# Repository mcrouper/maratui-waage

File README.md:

<p align="center">
    
    <br><br>
    
</p>

# MaraTUI

An embedded Rust TUI application for the **Lelit Mara X** espresso machine. Runs on an **ESP32** microcontroller driving an **ILI9341 320×240 display** over SPI, reads machine telemetry over UART, and publishes events to MQTT. Includes a host simulator mode for UI development without any hardware.

## Screenshots

| Loading | Dashboard | Debug |
|---------|-----------|-------|
|  |  |  |

## Screens

Navigation cycles between two main screens with a button press. The Debug screen is a hidden overlay.

### Dashboard

The primary screen. Shows all real-time machine data:

- **Mode banner** — COFFEE / STEAM / OFFLINE, color-coded
- **Boiler gauge** — current vs. target temperature with warm→ready color zones and a target marker
- **HX column** — heat-exchanger temperature with a vertical mini-gauge; ideal zone (90–95°C) is always visible
- **HEAT / PUMP indicators** — live status dots
- **Extraction timer** — large anti-aliased seconds counter; after the shot an assessment (GOOD, PERFECT, …) appears in its bottom border
- **Weight** — live shot weight in grams from the dual-HX711 scale, auto-tared the moment the pump starts
- **Shot gauge ("%")** — tracks extracted weight against a 40g target, not elapsed time
- **Shot quality label** — post-extraction assessment (UNDEREXTRACTED / GOOD / PERFECT / LONG SHOT / BLONDING) shown after the pump stops
- **Cup counter** — total shots brewed, received via MQTT
- **Tank water** — remaining water in the 2.3 L tank, tracked per pump run (weighed on the scale, or estimated from pump time) and saved across reboots; at 150 ml or less a popup asks to confirm the refill with a short press

### Graphs

Temperature history chart over a **5-minute rolling window** sampled at 1 Hz:

- Boiler current temperature (yellow)
- Boiler target temperature (red)
- HX temperature (blue)

### Debug (hidden overlay)

Accessible via long press. Shows Wi-Fi and MQTT connection statuses, device info (SSID, RSSI, IP, uptime, free heap), live raw UART frame with activity indicator, and the last 10 telemetry events.

## Getting Started

### Simulator

The simulator runs on your host machine using SDL2 for display emulation — no ESP32 needed.

**Prerequisites:** install SDL2 development libraries for your OS ([installation guide](https://docs.rs/crate/sdl2/latest/source/README.md)).

```bash
make sim          # auto-detects OS
```

Or use platform-specific cargo aliases:

| OS      | Command        |
|---------|----------------|
| Linux   | `cargo sim`    |
| macOS   | `cargo simmac` |
| Windows | `cargo simwin` |

**Keyboard controls:**

| Key          | Action                        |
|--------------|-------------------------------|
| Right / Left | Toggle Dashboard ↔ Graphs     |
| D            | Toggle Debug overlay          |
| Up           | Inject pump-on debug frame    |
| Down         | Inject normal debug frame     |
| Space        | Inject no-water debug frame   |
| M            | Publish manual MQTT event     |

### Device (ESP32)

**Prerequisites:** Rust with the `esp` toolchain channel (pinned in `rust-toolchain.toml`).

```bash
cargo run --release
```

Uses `espflash flash --monitor` as the runner. On startup the firmware:

1. Connects to Wi-Fi using embedded credentials
2. Starts the MQTT client and subscribes to `<prefix>/cup_counter`
3. Streams telemetry to `<prefix>/telemetry` (~1 Hz)
4. Publishes events (shot start/end, water refill, mode change) to `<prefix>/events`
5. Publishes device status (IP, RSSI, uptime, heap) to `<prefix>/status`

## Configuration

Copy `.env.example` to `.env` (git-ignored) and fill in your values:

```bash
cp .env.example .env
```

| Variable | Description |
|---|---|
| `MARATUI_WIFI_SSID` / `_PASSWORD` | Wi-Fi credentials (device build only) |
| `MARATUI_MQTT_ENABLED` | Set `true` to enable MQTT publishing |
| `MARATUI_MQTT_URL` | Broker URL, e.g. `mqtt://192.168.1.x:1883` |
| `MARATUI_MQTT_CLIENT_ID` | Unique client identifier |
| `MARATUI_MQTT_TOPIC_PREFIX` | Topic namespace prefix (default: `mara`) |

> [!NOTE]
> On the ESP32 build (`device` feature), `.env` is parsed by `build.rs` and values are embedded at compile time. On the simulator (`simulator` feature), env values are read at runtime and Wi-Fi is skipped — host networking is used directly for MQTT.

> [!WARNING]
> Wi-Fi and MQTT credentials are stored as plaintext `&'static str` in the flash image. Rotate credentials if the device is shared or its firmware is distributed. See the [Security Considerations](#security-considerations) section below.

## Home Assistant Integration

Build with `--features home-assistant` to enable MQTT Discovery publishing directly from the firmware — no Node-RED or other bridge required. On every MQTT connect, retained discovery configs are published and entities appear in Home Assistant automatically.

```bash
cargo run --release --features home-assistant   # flash
make sim-ha                                      # simulator
```

See [docs/home-assistant.md](docs/home-assistant.md) for the full entity list, MQTT topic reference, and cup counter setup.

## Web Dashboard

A standalone live dashboard page (temperatures with history, live scale weight, shot timer and weight curve, recent shots, events, device status) served by Node-RED at `http://<node-red-host>:1880/mara`, deployed with `python3 dashboard/deploy.py`. See [dashboard/README.md](dashboard/README.md).

## Color Editor

`python3 tools/color_editor.py` (Python 3 with Tkinter, no other dependencies) opens a drag-and-drop editor for the Dashboard and start screen colors: drag a swatch onto an element in the preview, then "Speichern" writes the palette constants back into `src/screens/dashboard.rs` and `src/screens/connecting.rs` — rebuild and flash to apply. Its "Startvideo" page plays the boot animation rendered by the firmware's own scene code (`examples/boot_frames.rs`, needs the host Rust toolchain), so animation changes can be previewed without flashing.

## Hardware

Target board: **ESP32 Type-C** with an external **ILI9341** 240×320 TFT display connected over SPI. There is a single physical button.

| Press             | Action                          |
|-------------------|---------------------------------|
| Short             | Zero the scale (confirms the tank refill while the low-water warning shows) |
| Double (fast 2x)  | Toggle Dashboard ↔ Graphs       |
| Double (on loading)| Toggle display backlight       |
| Long              | Enter / exit Debug overlay      |
| Hold (3s)         | Start the scale calibration wizard |

See [`hardware/`](hardware/) for the KiCad project, PCB renders, Gerber files, and full ESP32 pinout and display wiring.

### Scale (dual HX711 load cells)

Two independent HX711 amplifiers — one per drip-tray side — feed the live Weight display and
the weight-based shot gauge. Hold the button for 3s to run the calibration wizard (tare, then a
known reference weight, for each cell in turn); results persist to NVS. The scale also auto-tares
at boot and at the start of every shot; a short press zeroes it manually at any time. See
[`docs/hardware.md`](docs/hardware.md) for wiring and the full calibration walkthrough.

|  |  |  |
|:---:|:---:|:---:|

## Security Considerations

- **Credentials in flash** — Wi-Fi and MQTT credentials are embedded at compile time and extractable from the flash image with standard tools (`strings`, `binwalk`). Rotate if the device is shared.
- **Default broker is public** — `mqtt://broker.emqx.io:1883` is a free public broker with no access control. Set a private broker with authentication before deploying.
- **No TLS** — traffic is plaintext TCP. Switch to `mqtts://` and configure a CA certificate for production use.
- **Open Wi-Fi fallback** — if `MARATUI_WIFI_PASSWORD` is empty, `AuthMethod::None` is used (no encryption). A startup `warn!` names the SSID to make this explicit.

## Roadmap

- Offline mode using NVS storage

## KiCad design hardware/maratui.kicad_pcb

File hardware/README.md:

# MaraTUI PCB

Custom ESP32 controller board for the [Lelit Mara X](https://lelitcoffee.com/product/mara-x/) espresso machine.

## PCB Render

## Components

| Ref | Part | Link |
|-----|------|------|
| U1 | ILI9341 2.8" SPI TFT with touch | [Amazon TR](https://www.amazon.com.tr/2-8in%C3%A7-SPI-Dokunmatik-Ekran-Mod%C3%BCl%C3%BC/dp/B0GWFFJBZN) |
| U2 | ESP32-WROOM-32 | [Amazon TR](https://www.amazon.com.tr/ESP32-Wroom-32-Wifi-Bluetooth-Geli%C5%9Ftirme-Kart%C4%B1/dp/B0BT7SW1LF) |
| SW1 | Tactile switch | |
| J1 | Barrel jack (power) | |
| J2 | 3-pin connector (GND + UART) | |
| U3, U4 | HX711 load-cell amplifier (one per scale cell) | |

## Wiring

### SPI Display (ILI9341)

| Display Pin | ESP32 GPIO | Notes |
|-------------|------------|-------|
| SCK / CLK   | GPIO18     | VSPI CLK |
| SDA / MOSI  | GPIO21     | VSPI MOSI |
| DC / RS     | GPIO23     | Data/Command select |
| CS          | GPIO19     | Chip Select |
| RST / RESET | GPIO22     | Hardware reset |
| LED / BLK   | GPIO14     | Backlight (HIGH = on) |
| VCC         | 3.3V       | |
| GND         | GND        | |

### UART (Lelit Mara X telemetry)

| Function | ESP32 GPIO | Notes |
|----------|------------|-------|
| TX       | GPIO17     | UART1 TX |
| RX       | GPIO16     | UART1 RX |

### Scale (dual HX711 load cells)

| HX711 Pin    | ESP32 GPIO | Notes |
|--------------|------------|-------|
| DOUT (left)  | GPIO25     | Data, left load cell (input on ESP32) |
| SCK (left)   | GPIO26     | Clock, left load cell (output from ESP32) |
| DOUT (right) | GPIO32     | Data, right load cell (input on ESP32) |
| SCK (right)  | GPIO27     | Clock, right load cell (output from ESP32) |

Each HX711 has its **own** DOUT and SCK line (not shared) so the two cells can be clocked and
read independently — one under each side of the drip tray. See
[`docs/hardware.md`](../docs/hardware.md) for E+/E-/A+/A- load-cell wiring and the calibration
procedure.

### Button

| Button   | ESP32 GPIO | Notes |
|----------|------------|-------|
| SW1      | GPIO12     | Internal pull-up enabled |

Button connects GPIO to **GND** via a tactile switch (active LOW, falling-edge detection).

- Short press (< 500 ms): cycle screens (Dashboard ↔ Graphs)
- Double press (two short presses within 400 ms): zero the scale
- Long press (≥ 500 ms): toggle Debug screen
- Hold (3 s): start the scale calibration wizard

## Custom Libraries

Non-standard components are bundled in `lib/` so the project opens without missing library errors on any machine.

| File | Description |
|------|-------------|
| `lib/symbols/esp32_30pin.kicad_sym` | ESP32-WROOM-32 symbol |
| `lib/symbols/tft_320x240.kicad_sym` | ILI9341 320×240 symbol |
| `lib/footprints/maratui.pretty/ESP32_30pin.kicad_mod` | ESP32 footprint |
| `lib/footprints/maratui.pretty/TFT-320x240.kicad_mod` | TFT display footprint |

## Manufacturing

Gerber + drill files for fabrication: `gerbers/Mara_waage.zip` (single board, scale cells included; the same files also lie unpacked in `gerbers/`)

Tested with JLCPCB default 2-layer settings.

## 3D-Printed Parts (`3d-print/`)

Printable parts (STEP source + STL for slicing; versions in the file name):

| File | Description |
|------|-------------|
| `geh_koerper_V3.stp` / `geh_koerper_v3.stl` | Enclosure body (v3) — rear shell for ESP32 and PCB, cable/USB openings |
| `geh_deckel_V3.stp` / `geh_deckel_v3.stl` | Enclosure lid (v3) — front bezel with the display window |
| `doppelfuss_V2.stp` / `doppelfuss_v2.stl` | Double foot (v2) — mounts both load cells |
| `auflage_v2.stp` / `auflage_v2.stl` | Scale platform (v2) — print 2×, one per load cell |
| `staender_winkel.stp` / `staender_winkel.stl` | Display stand side bracket — print 2× |
| `strebe.stp` / `strebe.stl` | Cross strut joining the two stand brackets |
| `maratui_baugruppe.step` | Complete assembly: scale + display on its stand (load cells simplified) |
| `assemble.py` | Regenerates the assembly from the part STEPs (`pip install build123d`) |
| `render.py` | Renders the images below into `renders/` (`pip install build123d pyvista`) |

| | |
|---|---|
|  |  |
|  |  |

## CAD Models

| File | Description |
|------|-------------|
| `Plarine_cps.step` | Full board assembly (PCB + ESP32 DevKit + display + HX711 modules) as STEP |

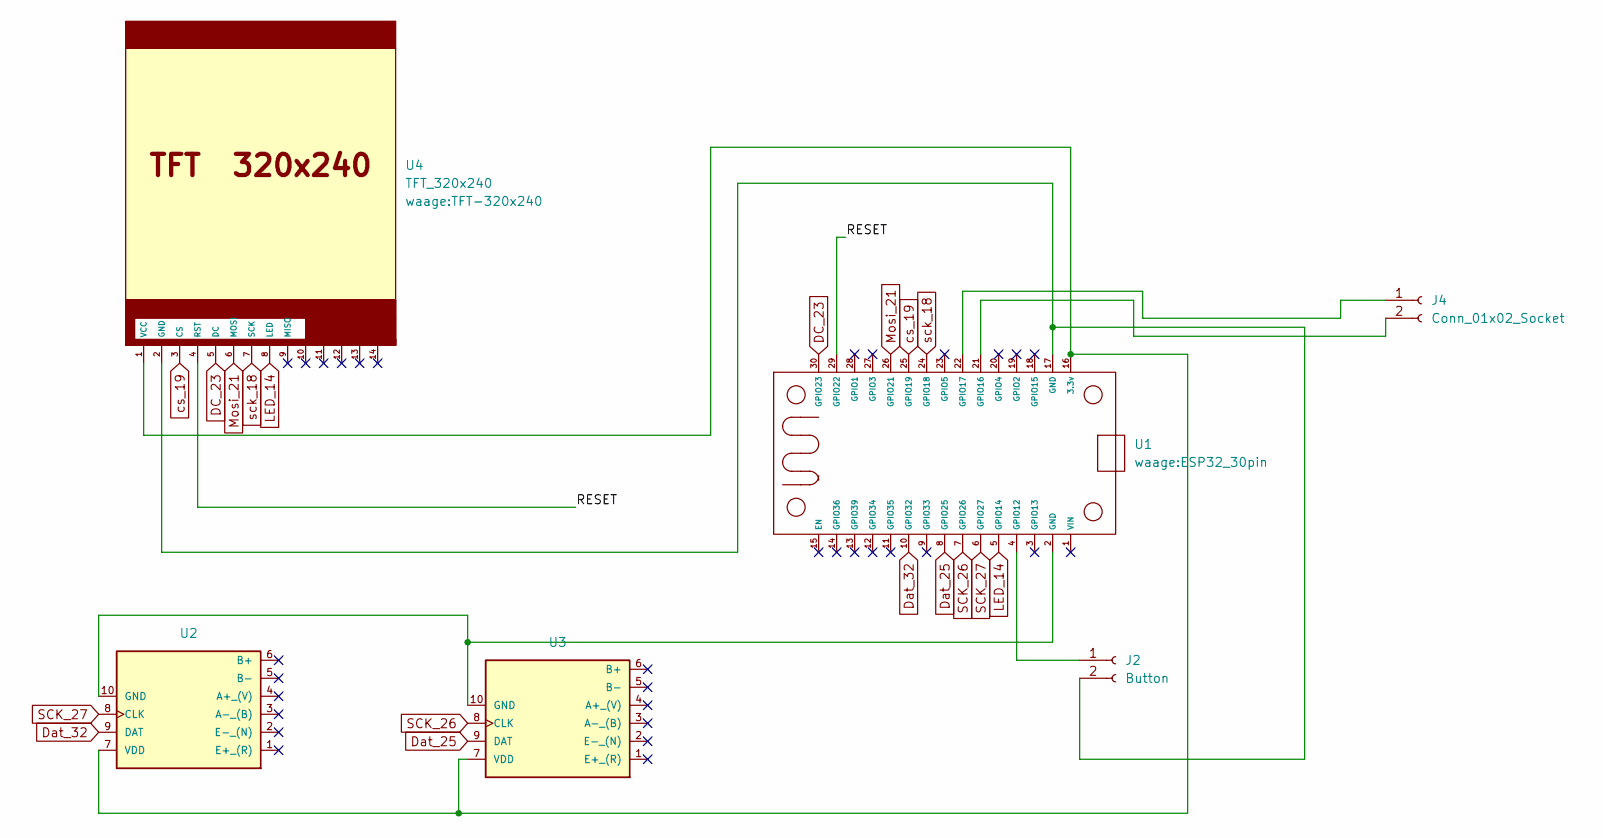
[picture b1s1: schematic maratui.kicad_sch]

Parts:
J2: Button; JST_EH_B2B-EH-A_1x02_P2.50mm_Vertical
J4: Conn_01x02_Socket; JST_EH_B2B-EH-A_1x02_P2.50mm_Vertical
U1: ESP32_30pin
U2, U3: HX711; HX711_module
U4: TFT_320x240; TFT-320x240

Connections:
/RESET: U1.29 (GPIO22), U4.4 (RST)
DC_23: U1.30 (GPIO23), U4.5 (DC)
Dat_25: U1.8 (GPIO25), U3.9 (DAT)
Dat_32: U1.10 (GPIO32), U2.9 (DAT)
LED_14: U1.5 (GPIO14), U4.8 (LED)
Mosi_21: U1.26 (GPIO21), U4.6 (MOSI)
unnamed: J2.1, U1.4 (GPIO12)
unnamed: J2.2, U1.17 (GND), U4.2 (GND)
unnamed: J4.1, U1.22 (GPIO17)
unnamed: J4.2, U1.21 (GPIO16)
unnamed: U1.16 (3.3v), U2.7 (VDD), U3.7 (VDD), U4.1 (VCC)
unnamed: U1.2 (GND), U2.10 (GND), U3.10 (GND)
SCK_26: U1.7 (GPIO26), U3.8 (CLK)
SCK_27: U1.6 (GPIO27), U2.8 (CLK)
cs_19: U1.25 (GPIO19), U4.3 (CS)
sck_18: U1.24 (GPIO18), U4.7 (SCK)

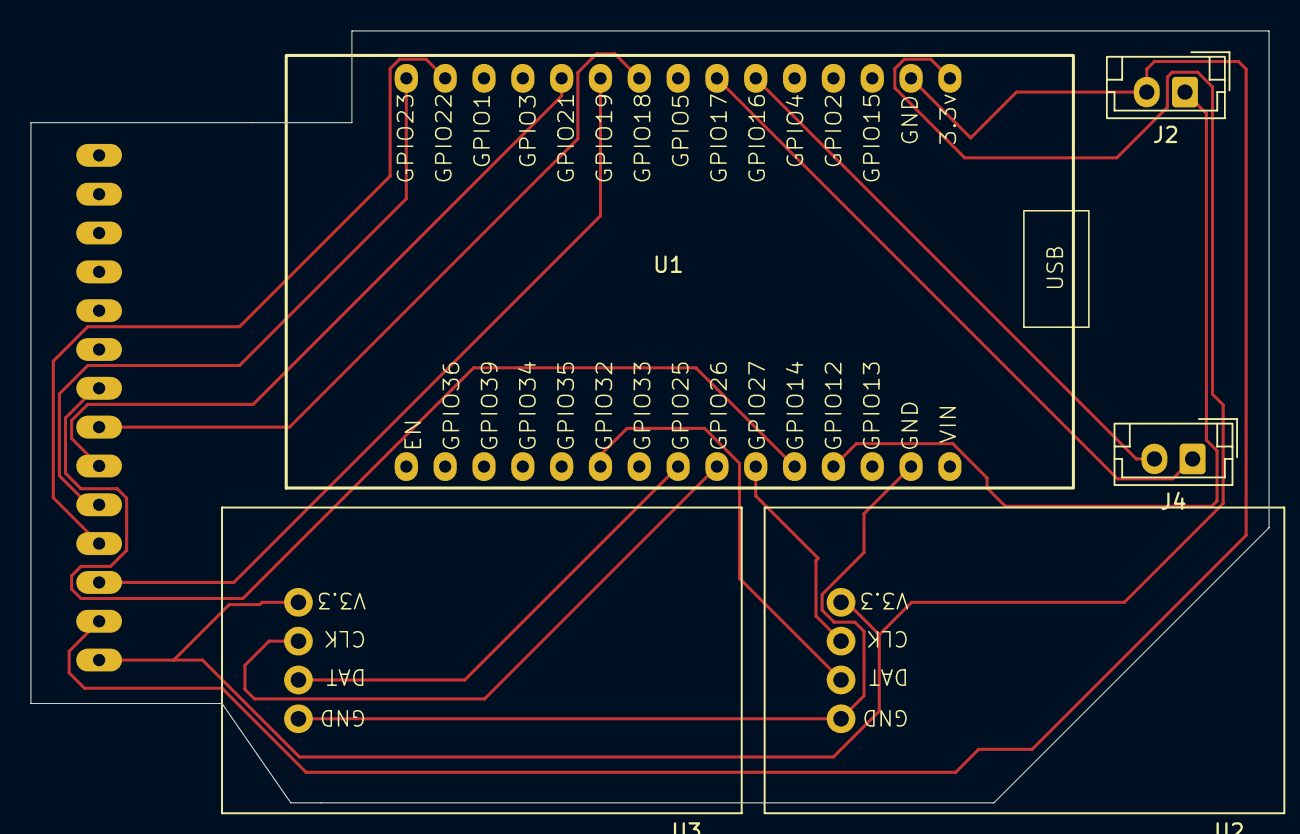
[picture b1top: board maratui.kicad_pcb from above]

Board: 2 copper layers, 81.0 x 50.5 mm, 6 parts (1 on the bottom side), 16 nets.

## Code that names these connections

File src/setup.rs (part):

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use crate::uart_reader::UartReader;
use display_interface_spi::SPIInterface;
use esp_idf_svc::eventloop::EspSystemEventLoop;
use esp_idf_svc::hal::gpio::{AnyIOPin, Gpio22, Gpio23, InterruptType, Output, PinDriver, Pull};
use esp_idf_svc::hal::prelude::*;
use esp_idf_svc::hal::spi::{SPI2, SpiConfig, SpiDeviceDriver, SpiDriver};
use esp_idf_svc::ipv4::{
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
type DisplayResult<'a> = anyhow::Result<
    Ili9341<
        SPIInterface<SpiDeviceDriver<'a, SpiDriver<'a>>, PinDriver<'a, Gpio23, Output>>,
        PinDriver<'a, Gpio22, Output>,
    >,
>;

fn get_ili9341<'a>(
    spi_p: SPI2,
    dc: esp_idf_svc::hal::gpio::Gpio23,
    mosi: esp_idf_svc::hal::gpio::Gpio21,
    sclk: esp_idf_svc::hal::gpio::Gpio18,
    cs: Option<esp_idf_svc::hal::gpio::Gpio19>,
    rst: esp_idf_svc::hal::gpio::Gpio22,
) -> DisplayResult<'a> {
    let sdi = Option::<AnyIOPin>::None; // MISO not used for display

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    let peripherals = Peripherals::take().unwrap();
    let modem = peripherals.modem;
    let spi_p = peripherals.spi2;
    let dc = peripherals.pins.gpio23;
    let mosi = peripherals.pins.gpio21;
    let sclk = peripherals.pins.gpio18;
    let cs = Some(peripherals.pins.gpio19);
    let rst = peripherals.pins.gpio22;
    let uart1 = peripherals.uart1;
    let uart_tx = peripherals.pins.gpio17;
    let uart_rx = peripherals.pins.gpio16;
    let button1_pin = peripherals.pins.gpio12;
    let hx711_dout_left = peripherals.pins.gpio25;
    let hx711_dout_right = peripherals.pins.gpio32;
    let hx711_sck_left = peripherals.pins.gpio26;
    let hx711_sck_right = peripherals.pins.gpio27;

    let mut display =
        get_ili9341(spi_p, dc, mosi, sclk, cs, rst).expect("Failed to initialize display");

    let mut backlight = PinDriver::output(peripherals.pins.gpio14).unwrap();
    backlight.set_high().unwrap();

    let mut button1 = PinDriver::input(button1_pin).unwrap();
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    let stage_start = Instant::now();
    let (tx, rx) = std::sync::mpsc::channel::<TelemetryFrame>();

    info!("Initializing UART1: TX=GPIO17, RX=GPIO16, baud=9600");
    let uart_reader = match UartReader::new(uart1, uart_tx, uart_rx) {
        Ok(reader) => {
            info!("UART1 initialized successfully");
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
